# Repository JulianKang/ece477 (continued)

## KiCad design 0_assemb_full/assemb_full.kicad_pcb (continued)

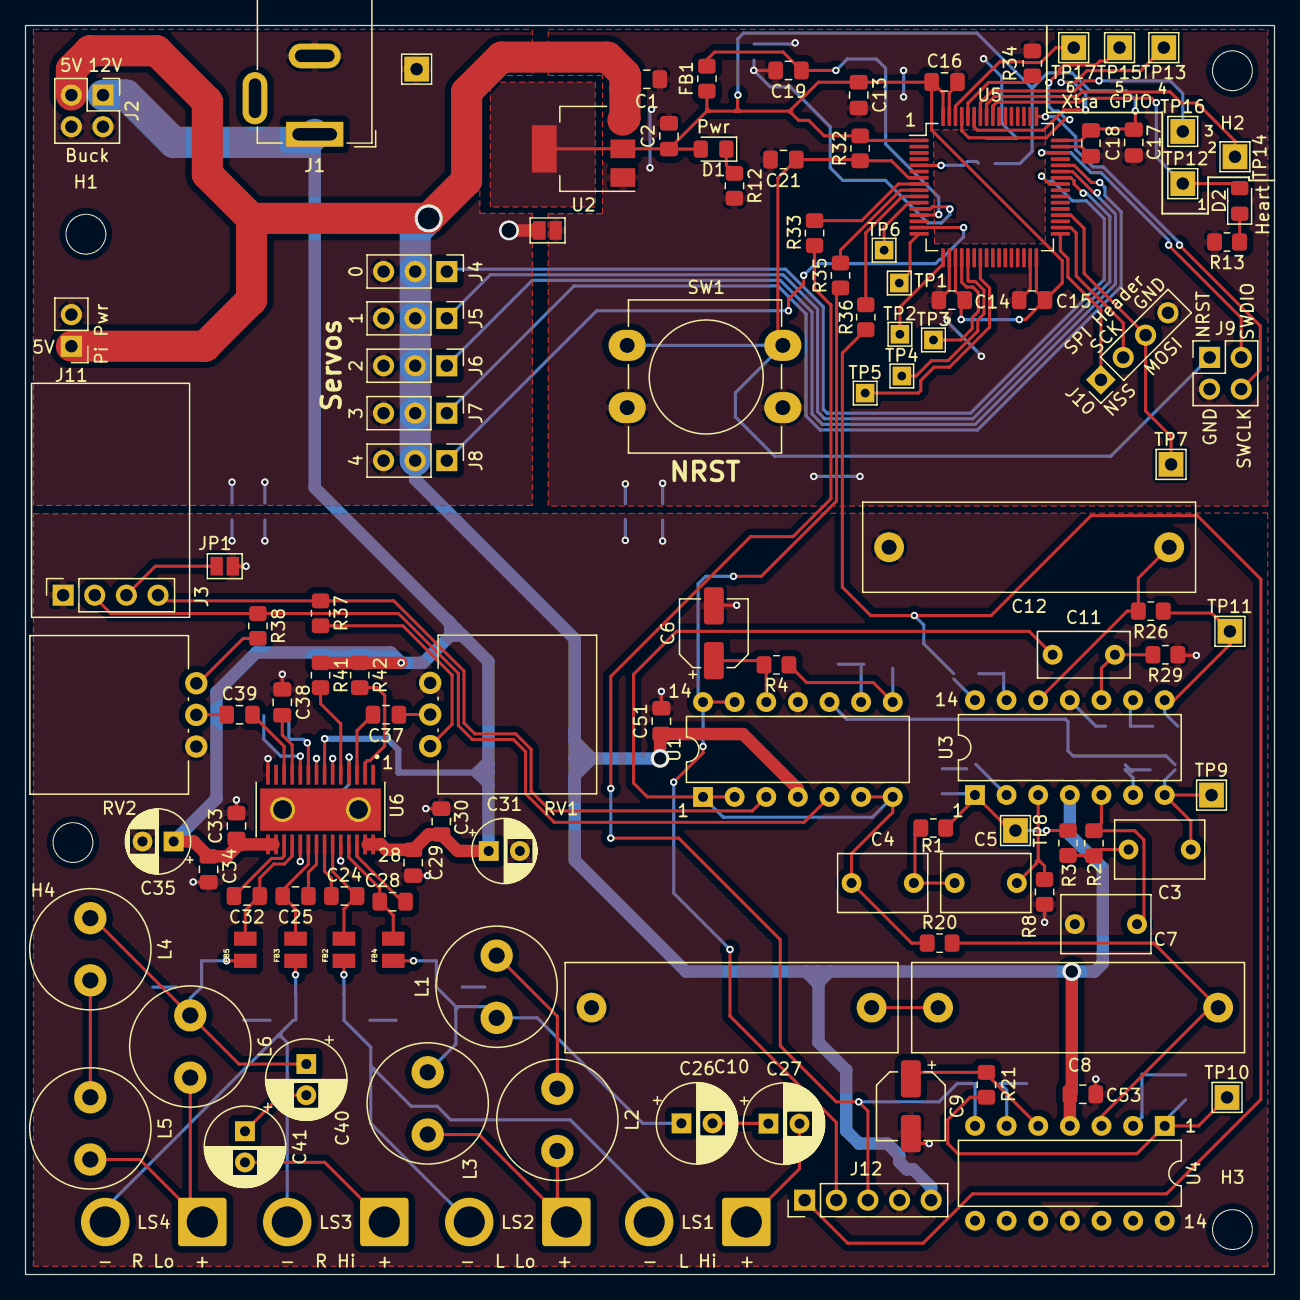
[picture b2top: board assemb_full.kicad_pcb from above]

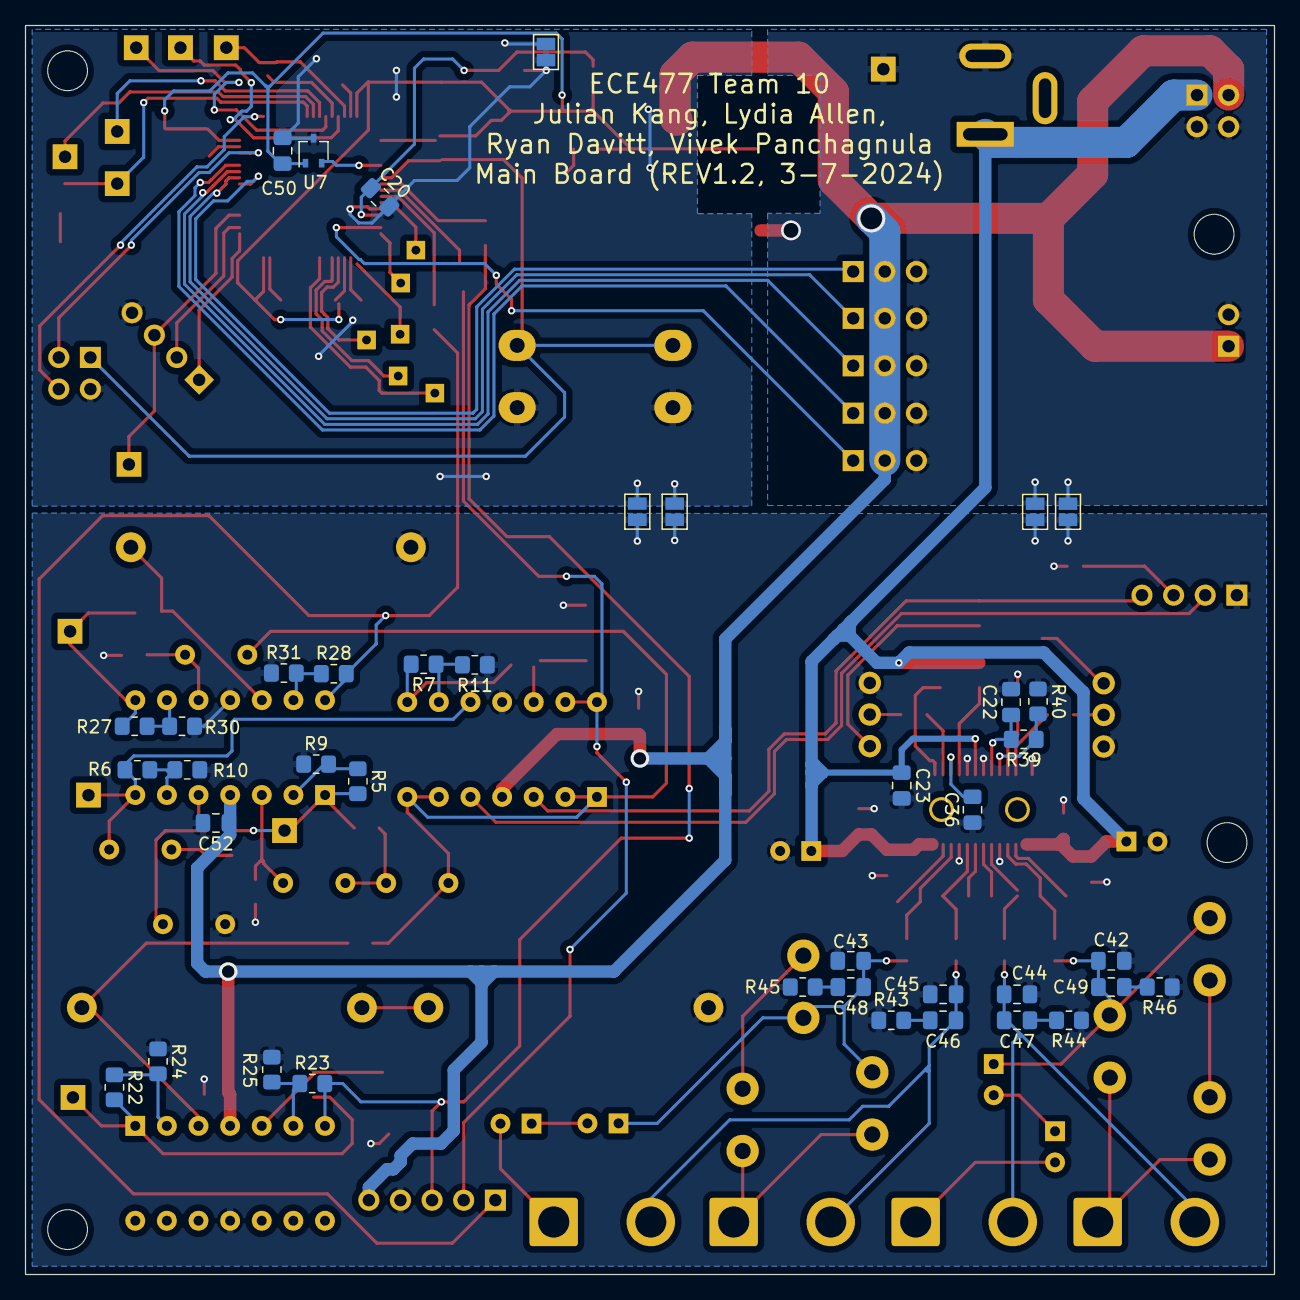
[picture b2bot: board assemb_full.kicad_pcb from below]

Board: 2 copper layers, 100.3 x 100.3 mm, 154 parts (35 on the bottom side), 100 nets.

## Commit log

2024-01-17 Initial KiCAD Uploads
2024-01-18 Updates to the filter
2024-01-19 An actually working LP Filter with a hopefully working comparator system for the LEDs.
2024-01-20 Fully functional LP Filter and Comparator-Resistor net with the LEDs
2024-01-23 Updating
2024-01-24 Added high-pass filter and made the whole system a bit more modular
2024-01-25 Low and high filter systems now ready
2024-01-26 Updated with values from the breadboard
2024-01-27 Now including band-pass, all circuits prototyped and proven to work
2024-02-06 Added the full schematic file and included the filters
2024-02-06 Added STM32F091RCTx symbol and power symbols
2024-02-07 Additional changes
2024-02-07 robot code commit
2024-02-07 assembly file initial commit
2024-02-11 Removed varistors, updated some STM32 connections
2024-02-13 Bandpass filter all set now!
2024-02-14 main.c code for Julian
2024-02-14 A bunch of changes to the schematics
2024-02-15 Updates to the filter system
2024-02-16 updated main with adc and changed servo functions
2024-02-17 Added amplifier circuit and the programming header.
2024-02-21 A lot of work done on the STM32 PCB layout.
2024-02-22 Pre-STM32 portion rework
2024-02-23 Some filter adjustments
2024-02-25 Active Filters layout added
2024-02-25 Full PCB layout complete
2024-02-26 Final adjustments
2024-02-26 Final changes to PCB after footprint tests.
2024-02-26 dance file parsing start
2024-02-27 Final adjustments (mostly silkscreen) pre-presentation
2024-03-05 Made adjustments according to presentation feedback. Almost ready for teaching team to look over.
2024-03-07 Fixed LED Board and added GND to SPI on Main Board
2024-03-24 main file with all functions
